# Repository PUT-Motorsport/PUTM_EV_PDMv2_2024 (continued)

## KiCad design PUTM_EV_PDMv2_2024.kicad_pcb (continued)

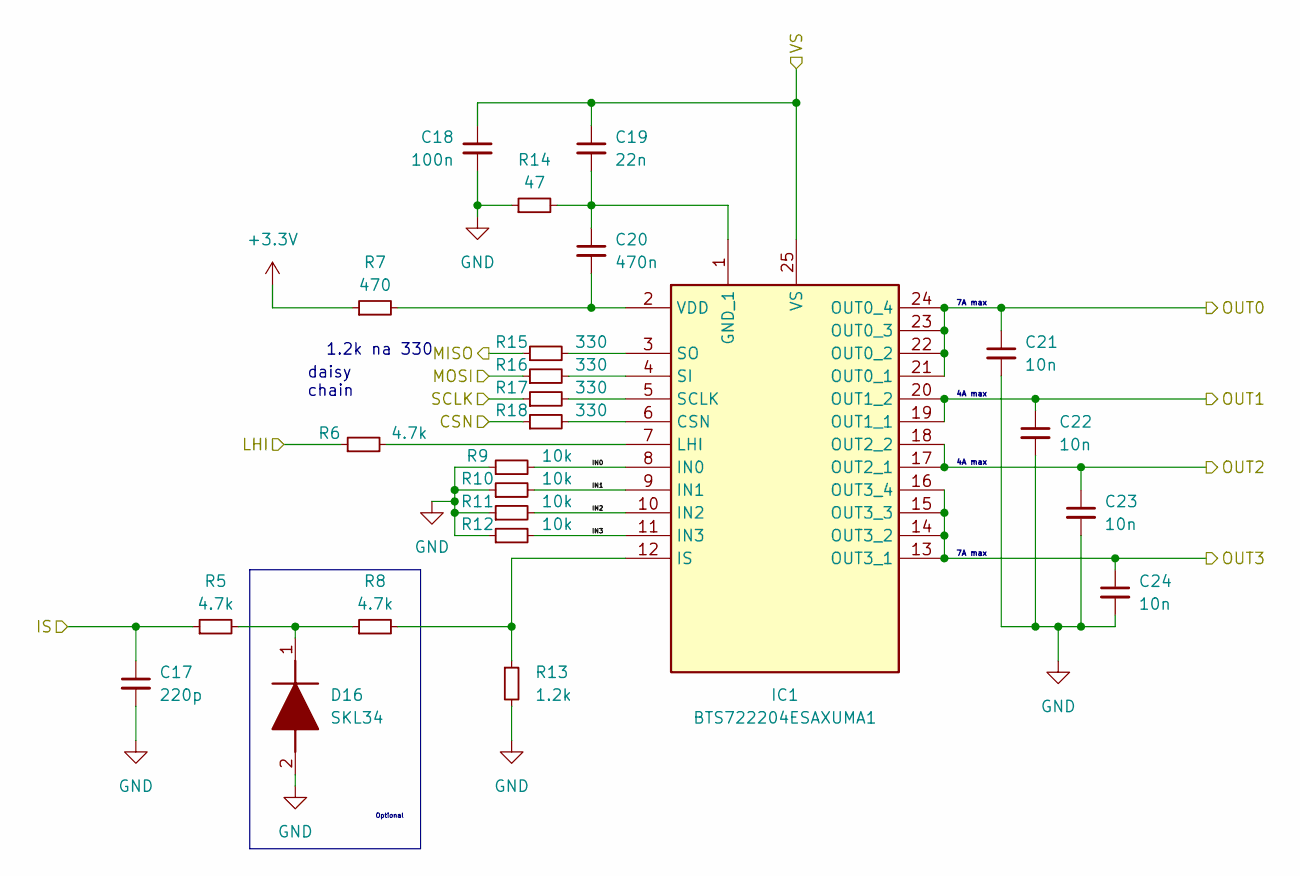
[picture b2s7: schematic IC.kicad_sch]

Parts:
C17: 220p; C_0603_1608Metric_Pad1.08x0.95mm_HandSolder
C18: 100n; C_0603_1608Metric_Pad1.08x0.95mm_HandSolder
C19: 22n; C_0603_1608Metric_Pad1.08x0.95mm_HandSolder
C20: 470n; C_0603_1608Metric_Pad1.08x0.95mm_HandSolder
C21, C22, C23, C24: 10n; C_0805_2012Metric
D16: SKL34; SODFL3718X140N; Mouser Part Number 637-SKL34
IC1: BTS722204ESAXUMA1; SOP65P600X115-25N; Mouser Part Number 726-BTS722204ESAXUMA
R5, R6, R8: 4.7k; R_0603_1608Metric_Pad0.98x0.95mm_HandSolder
R7: 470; R_0603_1608Metric_Pad0.98x0.95mm_HandSolder
R9, R10, R11, R12: 10k; R_0603_1608Metric_Pad0.98x0.95mm_HandSolder
R13: 1.2k; R_0603_1608Metric_Pad0.98x0.95mm_HandSolder
R14: 47; R_0603_1608Metric_Pad0.98x0.95mm_HandSolder
R15, R16, R17, R18: 330; R_0603_1608Metric_Pad0.98x0.95mm_HandSolder

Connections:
+3.3V: R7.1; also elsewhere on the board
+BATT: C18.1, C19.1, IC1.25 (VS); also elsewhere on the board
/Controllers/IC_1/IN0: IC1.8 (IN0), R9.2
/Controllers/IC_1/IN1: IC1.9 (IN1), R10.2
/Controllers/IC_1/IN2: IC1.10 (IN2), R11.2
/Controllers/IC_1/IN3: IC1.11 (IN3), R12.2
/Controllers/MISO_1: R15.1; also elsewhere on the board
/FUSE1_IS: C17.1, R5.1; also elsewhere on the board
/LHI_1: R6.1; also elsewhere on the board
/SPI1_MOSI: R16.1; also elsewhere on the board
/SPI1_NSS: R18.1; also elsewhere on the board
/SPI1_SCK: R17.1; also elsewhere on the board
GND: C17.2, C18.2, C21.2, C22.2, C23.2, C24.2, D16.2 (A), R9.1, R10.1, R11.1, R12.1, R13.2, R14.1; also elsewhere on the board
unnamed: D16.1 (K), R5.2, R8.1
unnamed: IC1.6 (CSN), R18.2
unnamed: C19.2, C20.1, IC1.1 (GND_1), R14.2
unnamed: IC1.12 (IS), R8.2, R13.1
unnamed: IC1.7 (LHI), R6.2
unnamed: IC1.5 (SCLK), R17.2
unnamed: IC1.4 (SI), R16.2
unnamed: IC1.3 (SO), R15.2
unnamed: C20.2, IC1.2 (VDD), R7.2
OUT1_0: C21.1, IC1.21 (OUT0_1), IC1.22 (OUT0_2), IC1.23 (OUT0_3), IC1.24 (OUT0_4); also elsewhere on the board
OUT1_1: C22.1, IC1.19 (OUT1_1), IC1.20 (OUT1_2); also elsewhere on the board
OUT1_2: C23.1, IC1.17 (OUT2_1), IC1.18 (OUT2_2); also elsewhere on the board
OUT1_3: C24.1, IC1.13 (OUT3_1), IC1.14 (OUT3_2), IC1.15 (OUT3_3), IC1.16 (OUT3_4); also elsewhere on the board

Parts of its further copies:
C29, C37, C45: 220p; C_0603_1608Metric_Pad1.08x0.95mm_HandSolder
C30, C38, C46: 100n; C_0603_1608Metric_Pad1.08x0.95mm_HandSolder
C31, C39, C47: 22n; C_0603_1608Metric_Pad1.08x0.95mm_HandSolder
C32, C40, C48: 470n; C_0603_1608Metric_Pad1.08x0.95mm_HandSolder
C33, C34, C35, C36, C41, C42, C43, C44, C49, C50, C51, C52: 10n; C_0805_2012Metric
D17, D18, D19: SKL34; SODFL3718X140N; Mouser Part Number 637-SKL34
IC2, IC3, IC4: BTS722204ESAXUMA1; SOP65P600X115-25N; Mouser Part Number 726-BTS722204ESAXUMA
R24, R25, R27, R38, R39, R41, R52, R53, R55: 4.7k; R_0603_1608Metric_Pad0.98x0.95mm_HandSolder
R26, R40, R54: 470; R_0603_1608Metric_Pad0.98x0.95mm_HandSolder
R28, R29, R30, R31, R42, R43, R44, R45, R56, R57, R58, R59: 10k; R_0603_1608Metric_Pad0.98x0.95mm_HandSolder
R32, R46, R60: 1.2k; R_0603_1608Metric_Pad0.98x0.95mm_HandSolder
R33, R47, R61: 47; R_0603_1608Metric_Pad0.98x0.95mm_HandSolder
R34, R35, R36, R37, R48, R49, R50, R51, R62, R63, R64, R65: 330; R_0603_1608Metric_Pad0.98x0.95mm_HandSolder

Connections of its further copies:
+3.3V: R26.1, R40.1, R54.1; also elsewhere on the board
+BATT: C30.1, C31.1, C38.1, C39.1, C46.1, C47.1, IC2.25 (VS), IC3.25 (VS), IC4.25 (VS); also elsewhere on the board
/Controllers/IC_2/IN0: IC2.8 (IN0), R28.2
/Controllers/IC_2/IN1: IC2.9 (IN1), R29.2
/Controllers/IC_2/IN2: IC2.10 (IN2), R30.2
/Controllers/IC_2/IN3: IC2.11 (IN3), R31.2
/Controllers/IC_3/IN0: IC3.8 (IN0), R42.2
/Controllers/IC_3/IN1: IC3.9 (IN1), R43.2
/Controllers/IC_3/IN2: IC3.10 (IN2), R44.2
/Controllers/IC_3/IN3: IC3.11 (IN3), R45.2
/Controllers/IC_4/IN0: IC4.8 (IN0), R56.2
/Controllers/IC_4/IN1: IC4.9 (IN1), R57.2
/Controllers/IC_4/IN2: IC4.10 (IN2), R58.2
/Controllers/IC_4/IN3: IC4.11 (IN3), R59.2
/Controllers/MISO_1: R35.1; also elsewhere on the board
/Controllers/MISO_2: R34.1, R49.1
/Controllers/MISO_3: R48.1, R63.1
/FUSE2_IS: C29.1, R24.1; also elsewhere on the board
/FUSE3_IS: C37.1, R38.1; also elsewhere on the board
/FUSE4_IS: C45.1, R52.1; also elsewhere on the board
/LHI_2: R25.1; also elsewhere on the board
/LHI_3: R39.1; also elsewhere on the board
/LHI_4: R53.1; also elsewhere on the board
/SPI1_MISO: R62.1; also elsewhere on the board
/SPI1_NSS: R37.1, R51.1, R65.1; also elsewhere on the board
/SPI1_SCK: R36.1, R50.1, R64.1; also elsewhere on the board
GND: C29.2, C30.2, C33.2, C34.2, C35.2, C36.2, C37.2, C38.2, C41.2, C42.2, C43.2, C44.2, C45.2, C46.2, C49.2, C50.2, C51.2, C52.2, D17.2 (A), D18.2 (A), D19.2 (A), R28.1, R29.1, R30.1, R31.1, R32.2, R33.1, R42.1, R43.1, R44.1, R45.1, R46.2, R47.1, R56.1, R57.1, R58.1, R59.1, R60.2, R61.1; also elsewhere on the board
unnamed: D17.1 (K), R24.2, R27.1
unnamed: D18.1 (K), R38.2, R41.1
unnamed: D19.1 (K), R52.2, R55.1
unnamed: IC2.6 (CSN), R37.2
unnamed: C31.2, C32.1, IC2.1 (GND_1), R33.2
unnamed: IC2.12 (IS), R27.2, R32.1
unnamed: IC2.7 (LHI), R25.2
unnamed: IC2.5 (SCLK), R36.2
unnamed: IC2.4 (SI), R35.2
unnamed: IC2.3 (SO), R34.2
unnamed: C32.2, IC2.2 (VDD), R26.2
unnamed: IC3.6 (CSN), R51.2
unnamed: C39.2, C40.1, IC3.1 (GND_1), R47.2
unnamed: IC3.12 (IS), R41.2, R46.1
unnamed: IC3.7 (LHI), R39.2
unnamed: IC3.5 (SCLK), R50.2
unnamed: IC3.4 (SI), R49.2
unnamed: IC3.3 (SO), R48.2
unnamed: C40.2, IC3.2 (VDD), R40.2
unnamed: IC4.6 (CSN), R65.2
unnamed: C47.2, C48.1, IC4.1 (GND_1), R61.2
unnamed: IC4.12 (IS), R55.2, R60.1
unnamed: IC4.7 (LHI), R53.2
unnamed: IC4.5 (SCLK), R64.2
unnamed: IC4.4 (SI), R63.2
unnamed: IC4.3 (SO), R62.2
unnamed: C48.2, IC4.2 (VDD), R54.2
OUT2_0: C33.1, IC2.21 (OUT0_1), IC2.22 (OUT0_2), IC2.23 (OUT0_3), IC2.24 (OUT0_4); also elsewhere on the board
OUT2_1: C34.1, IC2.19 (OUT1_1), IC2.20 (OUT1_2); also elsewhere on the board
OUT2_2: C35.1, IC2.17 (OUT2_1), IC2.18 (OUT2_2); also elsewhere on the board
OUT2_3: C36.1, IC2.13 (OUT3_1), IC2.14 (OUT3_2), IC2.15 (OUT3_3), IC2.16 (OUT3_4); also elsewhere on the board
OUT3_0: C41.1, IC3.21 (OUT0_1), IC3.22 (OUT0_2), IC3.23 (OUT0_3), IC3.24 (OUT0_4); also elsewhere on the board
OUT3_1: C42.1, IC3.19 (OUT1_1), IC3.20 (OUT1_2); also elsewhere on the board
OUT3_2: C43.1, IC3.17 (OUT2_1), IC3.18 (OUT2_2); also elsewhere on the board
OUT3_3: C44.1, IC3.13 (OUT3_1), IC3.14 (OUT3_2), IC3.15 (OUT3_3), IC3.16 (OUT3_4); also elsewhere on the board
OUT4_0: C49.1, IC4.21 (OUT0_1), IC4.22 (OUT0_2), IC4.23 (OUT0_3), IC4.24 (OUT0_4); also elsewhere on the board
OUT4_1: C50.1, IC4.19 (OUT1_1), IC4.20 (OUT1_2); also elsewhere on the board
OUT4_2: C51.1, IC4.17 (OUT2_1), IC4.18 (OUT2_2); also elsewhere on the board
OUT4_3: C52.1, IC4.13 (OUT3_1), IC4.14 (OUT3_2), IC4.15 (OUT3_3), IC4.16 (OUT3_4); also elsewhere on the board

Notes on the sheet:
7A max
Optional
4A max
daisy chain
1.2k na 330

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
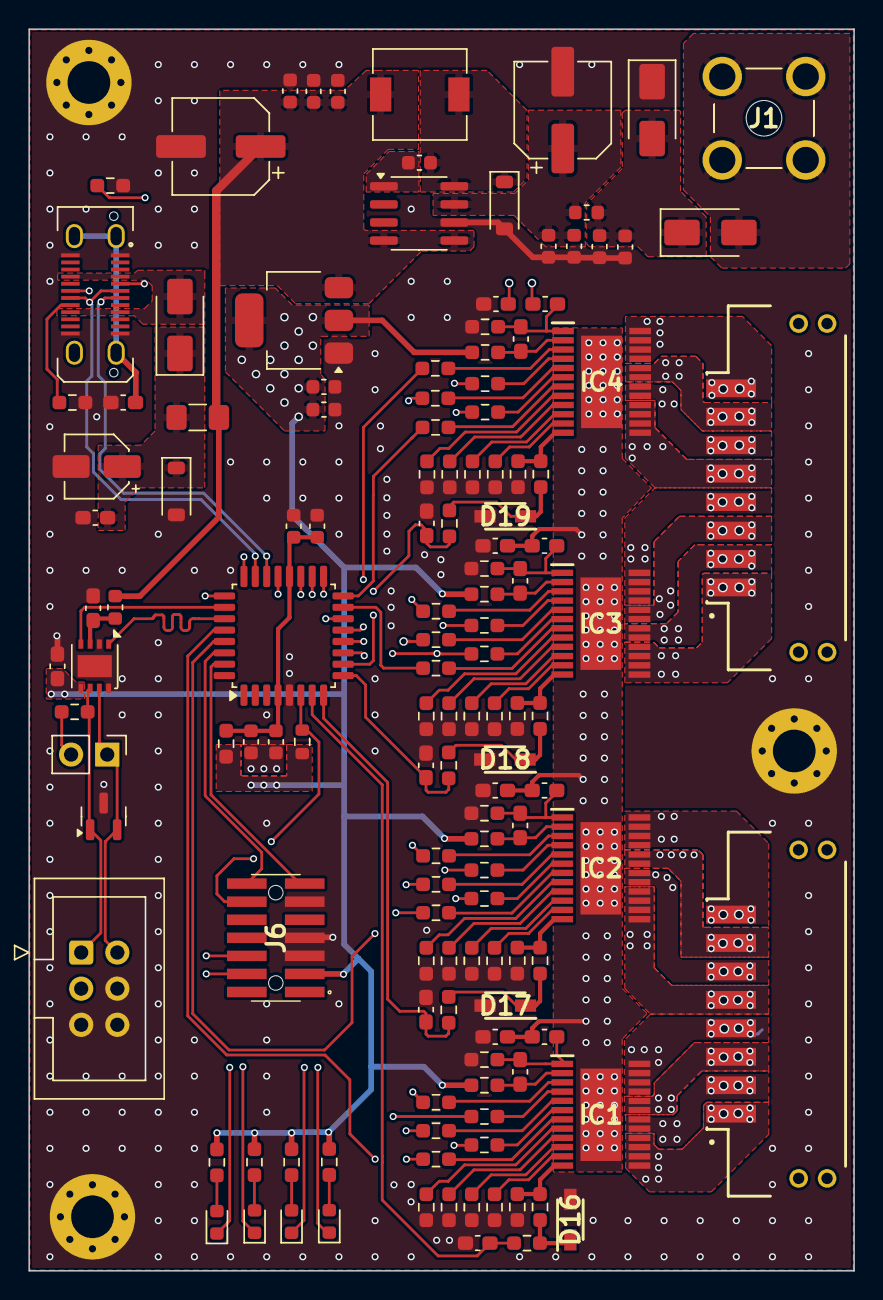
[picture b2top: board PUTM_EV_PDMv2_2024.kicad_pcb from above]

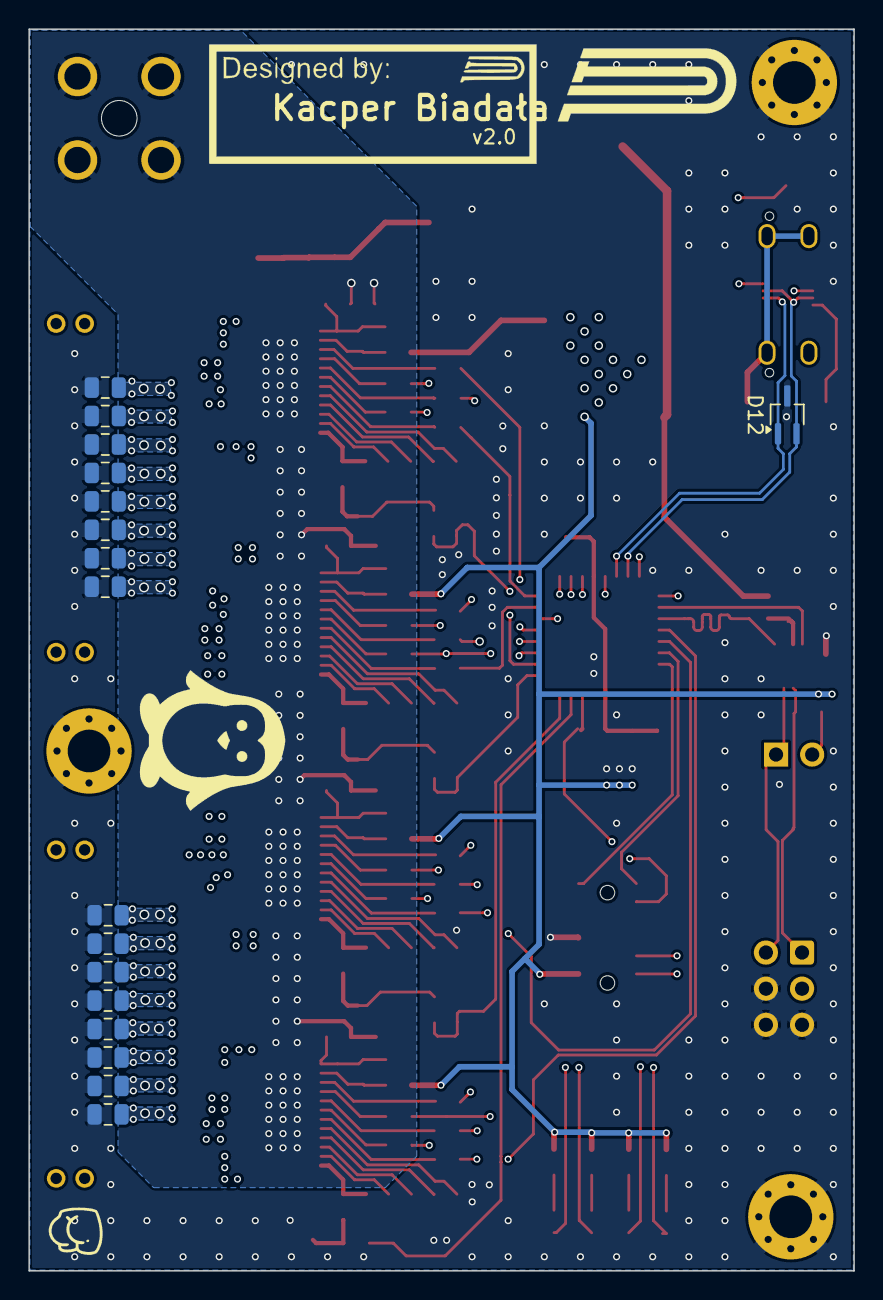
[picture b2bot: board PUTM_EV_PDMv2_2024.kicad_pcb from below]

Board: 4 copper layers, 58.0 x 87.3 mm, 152 parts (17 on the bottom side), 118 nets.

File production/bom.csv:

Designator,Footprint,Quantity,Value,LCSC Part #
"C1, C10, C13, C16, C18, C25, C26, C3, C30, C38, C46, C7, C8",0603,13,100n,
"C11, C15, C28, C5",0603,4,1u,
"C12, C53",0603,2,10n,
C14,CP_Elec_6.3x5.4,1,68u,
"C17, C29, C37, C45",0603,4,220p,
"C19, C31, C39, C47",0603,4,22n,
"C2, C4",0603,2,4.7u,
"C20, C32, C40, C48",0603,4,470n,
"C21, C22, C23, C24, C33, C34, C35, C36, C41, C42, C43, C44, C49, C50, C51, C52",0805,16,10n,
C27,CP_Elec_4x4.5,1,22u,
C6,0603,1,10u,
C9,CP_Elec_6.3x7.7,1,100u,
"D1, D2, D3, D4",0603,4,150060SS75000,
D10,D_SMA,1,0.1/1A,
D11,D_SOD-123,1,6V,
D12,SOT-323_SC-70_Handsoldering,1,TPD2E2U06QDCKRQ1,
"D16, D17, D18, D19",SODFL3718X140N,4,SKL34,
D5,D_SMA,1,SMAJ24CA-13-F,
D6,D_SOD-123,1,SS26FL,
D8,D_SMA,1,SS34ALH,
D9,SOT-23,1,PESD2CAN.215,
F1,1206,1,5V/0.5A,
FB2,0603,1,60R@100MHz,
"IC1, IC2, IC3, IC4",SOP65P600X115-25N,4,BTS722204ESAXUMA1,
J1,74650073R,1,74650073R,
J4,IDC-Header_2x03_P2.54mm_Vertical,1,Conn_01x06,
"J5, J8",SAMTEC_UMPT-08-01-L-RA-WT-P-TR,2,UMPT-08-01-L-RA-WT-P-TR,
J6,FTSH-107-XX-YYY-DV-K-A,1,FTSH-107-01-L-DV-K-A,
J7,USB_C_Receptacle_JAE_DX07S024WJ3R400,1,USB_C_Receptacle_USB2.0_14P,
JP1,PinHeader_1x02_P2.54mm_Vertical,1,Jumper_2_Bridged,
L1,0603,1,300n,
L2,L_6.3x6.3_H3,1,47u,
"R1, R2, R3, R4",0603,4,150,
"R10, R11, R12, R28, R29, R30, R31, R42, R43, R44, R45, R56, R57, R58, R59, R9",0603,16,10k,
"R13, R32, R46, R60",0603,4,1.2k,
"R14, R33, R47, R61",0603,4,47,
"R15, R16, R17, R18, R34, R35, R36, R37, R48, R49, R50, R51, R62, R63, R64, R65",0603,16,330,
R19,0603,1,100k,
R20,0603,1,0,
R21,0603,1,120,
"R22, R23",0603,2,5.1k,
"R24, R25, R27, R38, R39, R41, R5, R52, R53, R55, R6, R8",0603,12,4.7k,
"R26, R40, R54, R7",0603,4,470,
U1,LQFP-32_7x7mm_P0.8mm,1,STM32G0C1KCTxN,
U2,SOT-223-3_TabPin2,1,LD1117S33TR_SOT223,
U3,SOIC-8_3.9x4.9mm_P1.27mm,1,LM2675M-5.0/NOPB,
U4,DFN-8-1EP_3x3mm_P0.65mm_EP1.55x2.4mm,1,MCP2542FDxMF,

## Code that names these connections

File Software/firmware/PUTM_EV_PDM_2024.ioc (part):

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Mcu.Name=STM32G0C1K(C-E)TxN
Mcu.Package=LQFP32
Mcu.UserName=STM32G0C1KCTxN
PA0.GPIOParameters=GPIO_Label
PA0.GPIO_Label=FUSE1
PA0.Mode=IN0
PA0.Signal=ADC1_IN0
PA1.GPIOParameters=GPIO_Label
PA1.GPIO_Label=FUSE2
PA1.Mode=IN1
PA1.Signal=ADC1_IN1
PA10.GPIOParameters=GPIO_Label
PA10.GPIO_Label=LED1
PA10.Signal=GPIO_Output
PA13.Mode=Serial_Wire
PA13.Signal=SYS_SWDIO
PA14-BOOT0.Mode=Serial_Wire
PA14-BOOT0.Signal=SYS_SWCLK
PA2.GPIOParameters=GPIO_Label
PA2.GPIO_Label=FUSE3
PA2.Mode=IN2
PA2.Signal=ADC1_IN2
PA3.GPIOParameters=GPIO_Label
PA3.GPIO_Label=FUSE4
PA3.Mode=IN3
PA3.Signal=ADC1_IN3
PA4.GPIOParameters=GPIO_Label
PA4.GPIO_Label=SPI1_SS
PA4.Signal=GPIO_Output
PA5.Mode=Full_Duplex_Master
PA5.Signal=SPI1_SCK
PA6.Mode=Full_Duplex_Master
PA6.Signal=SPI1_MISO
PA7.Mode=Full_Duplex_Master
PA7.Signal=SPI1_MOSI
PA8.GPIOParameters=GPIO_Label
PA8.GPIO_Label=LED3
PA8.Signal=GPIO_Output
PA9.GPIOParameters=GPIO_Label
PA9.GPIO_Label=LED2
PA9.Signal=GPIO_Output
PB0.GPIOParameters=GPIO_Label
PB0.GPIO_Label=LHI_3
PB0.Signal=GPIO_Output
PB1.GPIOParameters=GPIO_Label
PB1.GPIO_Label=LHI_4
PB1.Signal=GPIO_Output
PB15.GPIOParameters=GPIO_Label
PB15.GPIO_Label=LED4
PB15.Signal=GPIO_Output
PB6.Signal=USART1_TX
PB7.Signal=USART1_RX
PD0.GPIOParameters=GPIO_Speed,PinState
PD0.GPIO_Speed=GPIO_SPEED_FREQ_VERY_HIGH
PD0.Mode=FDCAN_Activate
PD0.PinState=GPIO_PIN_RESET
PD0.Signal=FDCAN1_RX
PD1.GPIOParameters=GPIO_Speed
PD1.GPIO_Speed=GPIO_SPEED_FREQ_VERY_HIGH
PD1.Mode=FDCAN_Activate
PD1.Signal=FDCAN1_TX
PD2.GPIOParameters=GPIO_Label
PD2.GPIO_Label=LHI_1
PD2.Signal=GPIO_Output
PD3.GPIOParameters=GPIO_Label
PD3.GPIO_Label=LHI_2
PD3.Signal=GPIO_Output
RCC.HSE_VALUE=8000000
RCC.SYSCLKFreq_VALUE=64000000
RCC.SYSCLKSource=RCC_SYSCLKSOURCE_PLLCLK
board=custom

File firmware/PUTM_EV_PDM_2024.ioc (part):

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Mcu.Name=STM32G0C1K(C-E)TxN
Mcu.Package=LQFP32
Mcu.UserName=STM32G0C1KCTxN
PA0.GPIOParameters=GPIO_Label
PA0.GPIO_Label=IC0
PA0.Mode=IN0
PA0.Signal=ADC1_IN0
PA1.GPIOParameters=GPIO_Label
PA1.GPIO_Label=IC1
PA1.Mode=IN1
PA1.Signal=ADC1_IN1
PA10.GPIOParameters=GPIO_Label
PA10.GPIO_Label=LED2
PA10.Signal=GPIO_Output
PA13.Mode=Serial_Wire
PA13.Signal=SYS_SWDIO
PA14-BOOT0.Mode=Serial_Wire
PA14-BOOT0.Signal=SYS_SWCLK
PA2.GPIOParameters=GPIO_Label
PA2.GPIO_Label=IC2
PA2.Mode=IN2
PA2.Signal=ADC1_IN2
PA3.GPIOParameters=GPIO_Label
PA3.GPIO_Label=IC3
PA3.Mode=IN3
PA3.Signal=ADC1_IN3
PA4.GPIOParameters=PinState,GPIO_Label
PA4.GPIO_Label=SPI1_NSS
PA4.PinState=GPIO_PIN_SET
PA4.Signal=GPIO_Output
PA5.Mode=Full_Duplex_Master
PA5.Signal=SPI1_SCK
PA6.Mode=Full_Duplex_Master
PA6.Signal=SPI1_MISO
PA7.Mode=Full_Duplex_Master
PA7.Signal=SPI1_MOSI
PA8.GPIOParameters=GPIO_Label
PA8.GPIO_Label=LED0
PA8.Signal=GPIO_Output
PA9.GPIOParameters=GPIO_Label
PA9.GPIO_Label=LED1
PA9.Signal=GPIO_Output
PB0.GPIOParameters=GPIO_Label
PB0.GPIO_Label=LHI_3
PB0.Signal=GPIO_Output
PB1.GPIOParameters=GPIO_Label
PB1.GPIO_Label=LHI_4
PB1.Signal=GPIO_Output
PB15.GPIOParameters=GPIO_Label
PB15.GPIO_Label=LED3
PB15.Signal=GPIO_Output
PC14-OSC32_IN\ (PC14).GPIOParameters=PinState,GPIO_Label
PC14-OSC32_IN\ (PC14).GPIO_Label=CAN_STBY
PC14-OSC32_IN\ (PC14).PinState=GPIO_PIN_RESET
PC14-OSC32_IN\ (PC14).Signal=GPIO_Output
PD0.GPIOParameters=GPIO_Speed,PinState
PD0.GPIO_Speed=GPIO_SPEED_FREQ_VERY_HIGH
PD0.Mode=FDCAN_Activate
PD0.PinState=GPIO_PIN_RESET
PD0.Signal=FDCAN1_RX
PD1.GPIOParameters=GPIO_Speed
PD1.GPIO_Speed=GPIO_SPEED_FREQ_VERY_HIGH
PD1.Mode=FDCAN_Activate
PD1.Signal=FDCAN1_TX
PD2.GPIOParameters=GPIO_Label
PD2.GPIO_Label=LHI_1
PD2.Signal=GPIO_Output
PD3.GPIOParameters=GPIO_Label
PD3.GPIO_Label=LHI_2
PD3.Signal=GPIO_Output
RCC.HSE_VALUE=8000000
RCC.SYSCLKFreq_VALUE=32000000
RCC.SYSCLKSource=RCC_SYSCLKSOURCE_PLLCLK
board=custom

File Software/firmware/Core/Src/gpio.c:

/* USER CODE BEGIN Header */
/**
  ******************************************************************************
  * @file    gpio.c
  * @brief   This file provides code for the configuration
  *          of all used GPIO pins.
  ******************************************************************************
  * @attention
  *
  * Copyright (c) 2024 STMicroelectronics.
  * All rights reserved.
  *
  * This software is licensed under terms that can be found in the LICENSE file
  * in the root directory of this software component.
  * If no LICENSE file comes with this software, it is provided AS-IS.
  *
  ******************************************************************************
  */
/* USER CODE END Header */

/* Includes ------------------------------------------------------------------*/
#include "gpio.h"

/* USER CODE BEGIN 0 */

/* USER CODE END 0 */

/*----------------------------------------------------------------------------*/
/* Configure GPIO                                                             */
/*----------------------------------------------------------------------------*/
/* USER CODE BEGIN 1 */

/* USER CODE END 1 */

/** Configure pins as
        * Analog
        * Input
        * Output
        * EVENT_OUT
        * EXTI
        * Free pins are configured automatically as Analog (this feature is enabled through
        * the Code Generation settings)
     PB6   ------> USART1_TX
     PB7   ------> USART1_RX
*/
void MX_GPIO_Init(void)
{

  GPIO_InitTypeDef GPIO_InitStruct = {0};

  /* GPIO Ports Clock Enable */
  __HAL_RCC_GPIOB_CLK_ENABLE();
  __HAL_RCC_GPIOC_CLK_ENABLE();
  __HAL_RCC_GPIOF_CLK_ENABLE();
  __HAL_RCC_GPIOA_CLK_ENABLE();
  __HAL_RCC_GPIOD_CLK_ENABLE();

  /*Configure GPIO pin Output Level */
  HAL_GPIO_WritePin(GPIOA, SPI1_SS_Pin|LED3_Pin|LED2_Pin|LED1_Pin, GPIO_PIN_RESET);

  /*Configure GPIO pin Output Level */
  HAL_GPIO_WritePin(GPIOB, LHI_3_Pin|LHI_4_Pin|LED4_Pin, GPIO_PIN_RESET);

  /*Configure GPIO pin Output Level */
  HAL_GPIO_WritePin(GPIOD, LHI_1_Pin|LHI_2_Pin, GPIO_PIN_RESET);

  /*Configure GPIO pins : PB9 PB8 */
  GPIO_InitStruct.Pin = GPIO_PIN_9|GPIO_PIN_8;
  GPIO_InitStruct.Mode = GPIO_MODE_ANALOG;
  GPIO_InitStruct.Pull = GPIO_NOPULL;
  HAL_GPIO_Init(GPIOB, &GPIO_InitStruct);

  /*Configure GPIO pins : PC14 PC15 */
  GPIO_InitStruct.Pin = GPIO_PIN_14|GPIO_PIN_15;
  GPIO_InitStruct.Mode = GPIO_MODE_ANALOG;
  GPIO_InitStruct.Pull = GPIO_NOPULL;
  HAL_GPIO_Init(GPIOC, &GPIO_InitStruct);

  /*Configure GPIO pin : PF2 */
  GPIO_InitStruct.Pin = GPIO_PIN_2;
  GPIO_InitStruct.Mode = GPIO_MODE_ANALOG;
  GPIO_InitStruct.Pull = GPIO_NOPULL;
  HAL_GPIO_Init(GPIOF, &GPIO_InitStruct);

  /*Configure GPIO pins : PAPin PAPin PAPin PAPin */
  GPIO_InitStruct.Pin = SPI1_SS_Pin|LED3_Pin|LED2_Pin|LED1_Pin;
  GPIO_InitStruct.Mode = GPIO_MODE_OUTPUT_PP;
  GPIO_InitStruct.Pull = GPIO_NOPULL;
  GPIO_InitStruct.Speed = GPIO_SPEED_FREQ_LOW;
  HAL_GPIO_Init(GPIOA, &GPIO_InitStruct);

  /*Configure GPIO pins : PBPin PBPin PBPin */
  GPIO_InitStruct.Pin = LHI_3_Pin|LHI_4_Pin|LED4_Pin;
  GPIO_InitStruct.Mode = GPIO_MODE_OUTPUT_PP;
  GPIO_InitStruct.Pull = GPIO_NOPULL;
  GPIO_InitStruct.Speed = GPIO_SPEED_FREQ_LOW;
  HAL_GPIO_Init(GPIOB, &GPIO_InitStruct);

  /*Configure GPIO pins : PA11 PA12 */
  GPIO_InitStruct.Pin = GPIO_PIN_11|GPIO_PIN_12;
  GPIO_InitStruct.Mode = GPIO_MODE_ANALOG;
  GPIO_InitStruct.Pull = GPIO_NOPULL;
  HAL_GPIO_Init(GPIOA, &GPIO_InitStruct);

  /*Configure GPIO pins : PDPin PDPin */
  GPIO_InitStruct.Pin = LHI_1_Pin|LHI_2_Pin;
  GPIO_InitStruct.Mode = GPIO_MODE_OUTPUT_PP;
  GPIO_InitStruct.Pull = GPIO_NOPULL;
  GPIO_InitStruct.Speed = GPIO_SPEED_FREQ_LOW;
  HAL_GPIO_Init(GPIOD, &GPIO_InitStruct);

  /*Configure GPIO pins : PB6 PB7 */
  GPIO_InitStruct.Pin = GPIO_PIN_6|GPIO_PIN_7;
  GPIO_InitStruct.Mode = GPIO_MODE_AF_PP;
  GPIO_InitStruct.Pull = GPIO_NOPULL;
  GPIO_InitStruct.Speed = GPIO_SPEED_FREQ_LOW;
  GPIO_InitStruct.Alternate = GPIO_AF0_USART1;
  HAL_GPIO_Init(GPIOB, &GPIO_InitStruct);

}

/* USER CODE BEGIN 2 */

/* USER CODE END 2 */

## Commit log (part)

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2024-11-05 New project, started scheme
2024-11-11 Finished schematic
    Added UCB C connection
    Added CAN
    Power ICs schematic fixed
2024-11-14 Minor fixes
2024-11-20 Footprint changes + started PCB
2024-11-26 Minor changes
2024-12-08 Layout done
    Added layout
2024-12-09 Minor changes
    Added battery zone on the f.cu
    Easier connector soldering (additional pads)
    Changed 3.3V layer
2024-12-09 Production
2024-12-13 Minor fixes
    added USBc tvs
2024-12-18 Rounded
2025-03-18 last unchecked harware update - fix dir structure
2025-03-18 soft branch create
2025-03-29 Single channel closing
    Added functionality of closing one channel when detecting overcurrent and opening, when the overcurrent is no longer detected
2025-04-15 Working closing multiple channels
2025-04-15 Reopening logic
    - reopening all channels simultaneously 5s after detection of the first overcurrent
    - changed thresholds to global variables
2025-05-09 Dummy CAN for testing
2025-05-15 CAN library added
2025-05-15 working CAN library added
2025-05-15 Added CAN receiving
2025-05-15 Added CAN communication (to be tested)
2025-05-18 Auto stash before merge of "soft-v1.1.0" and "origin/soft-v1.1.0"
2025-05-20 Status added to CAN
2025-05-20 Added current readings to CAN (can not tested)
    - Added system overview and comments
    - Added CAN current readings
2025-05-26 CAN config CubeMX for 1MB/s
2025-05-27 Changed current readings to amperes
    The thresholds and valuse stored from current reading is now stored in amperes with 0.1A accuracy
2025-05-27 Fix Can
2025-05-27 Fix Can
    IMPORTANT COMMIT
2025-06-01 Updated retry + RTD and temp functionality
    Not checked!
    -Retry logic updated
    now each channel state is stored individually, and the channels reset every 5s twice.
    -CAN RTD and temp functionality
    when RTD is off, the pumps and fans are off, however if the temperature rises above 30, they change to ON. With RTD on they are constantly ON.
2025-06-21 Correct current readings
    - Created new linear function for channels 1 and 2. Channels 0 and 3 stay the same
    - Channels reopen 5 times every 5s, then turn off permanently
2025-08-23 Sync for FSG2025
2025-12-05 Changed CAN to isolated and added a new board-to-board plug
2025-12-17 NEW SCHEMATIC
2025-12-17 NEWER SCHEMATIC
2026-03-24 new pcb layout & can coppied from steeringwheel
2026-03-24 pcb layout-battery conn updated
2026-03-24 pcb layout-power section 5V update
2026-03-29 pcb layout - controlers power->battery, added mounting holes
2026-05-13 cmake port
2026-05-14 cube->cmake port, current calc fix, spi datalength fix, hard-v1.1.0 sync
2026-05-16 extracted BTS72220 logic, added classess for ics and channels
2026-05-16 added methods for current update
2026-05-17 added retry logic
2026-05-18 added automatic spi buffer reverse for daisy chain
2026-05-18 improved retry
2026-05-18 added system status update logic
2026-05-20 changed current to uint16_t
2026-05-21 imported new can
2026-05-21 added can rx cb
2026-05-22 added can send
2026-05-23 deleted old can library, extracted pdu logic to its own file
2026-05-23 added fan logic
2026-05-24 added docs
2026-05-25 fixed array reverse in txrx function
2026-05-25 updated can transmission for new dbc
2026-05-25 fixed retry count reset bug
2026-05-26 fixed channel status error
2026-05-27 current sense calibration
2026-06-01 deleted bitfields
2026-06-19 fixed can rx cb
2026-06-20 added can init XD
2026-06-20 added can filter config
2026-06-20 deleted filters
2026-06-21 fixed clocks
